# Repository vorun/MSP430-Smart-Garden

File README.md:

# MSP430-Smart-Garden

This project is a smart agricultural system based on C# using MSP430 microcontroller.

- Data coming from 3 sensors gets sent serially using bluetooth module from msp430 to computer and displayed at the
screen.

- Devices connected to msp430 which are lamp, fan, heater and 2 water pumps can be controlled from the
computer. Each button sends a different character and msp430 does operations acording to character it 
receives. Msp430 generates 3 different pwm signals to control fan and lamp for each setting which are 
low, medium and high. Heater can be oppened and closed. 2 water pumps can be oppened for 3 different 
amount times which are 3 seconds, 7 seconds and 10 seconds.

- Pin connections and circuit design/PCB of the project can be found at the 
"C# Based Smart Gardener Final PCB" folder.

For demo: https://www.youtube.com/watch?v=NzMayukbllw

Note
- Updated PCB with MOSFETs and gate drivers.

Orhun Dabak/Ahmet Özbaysar

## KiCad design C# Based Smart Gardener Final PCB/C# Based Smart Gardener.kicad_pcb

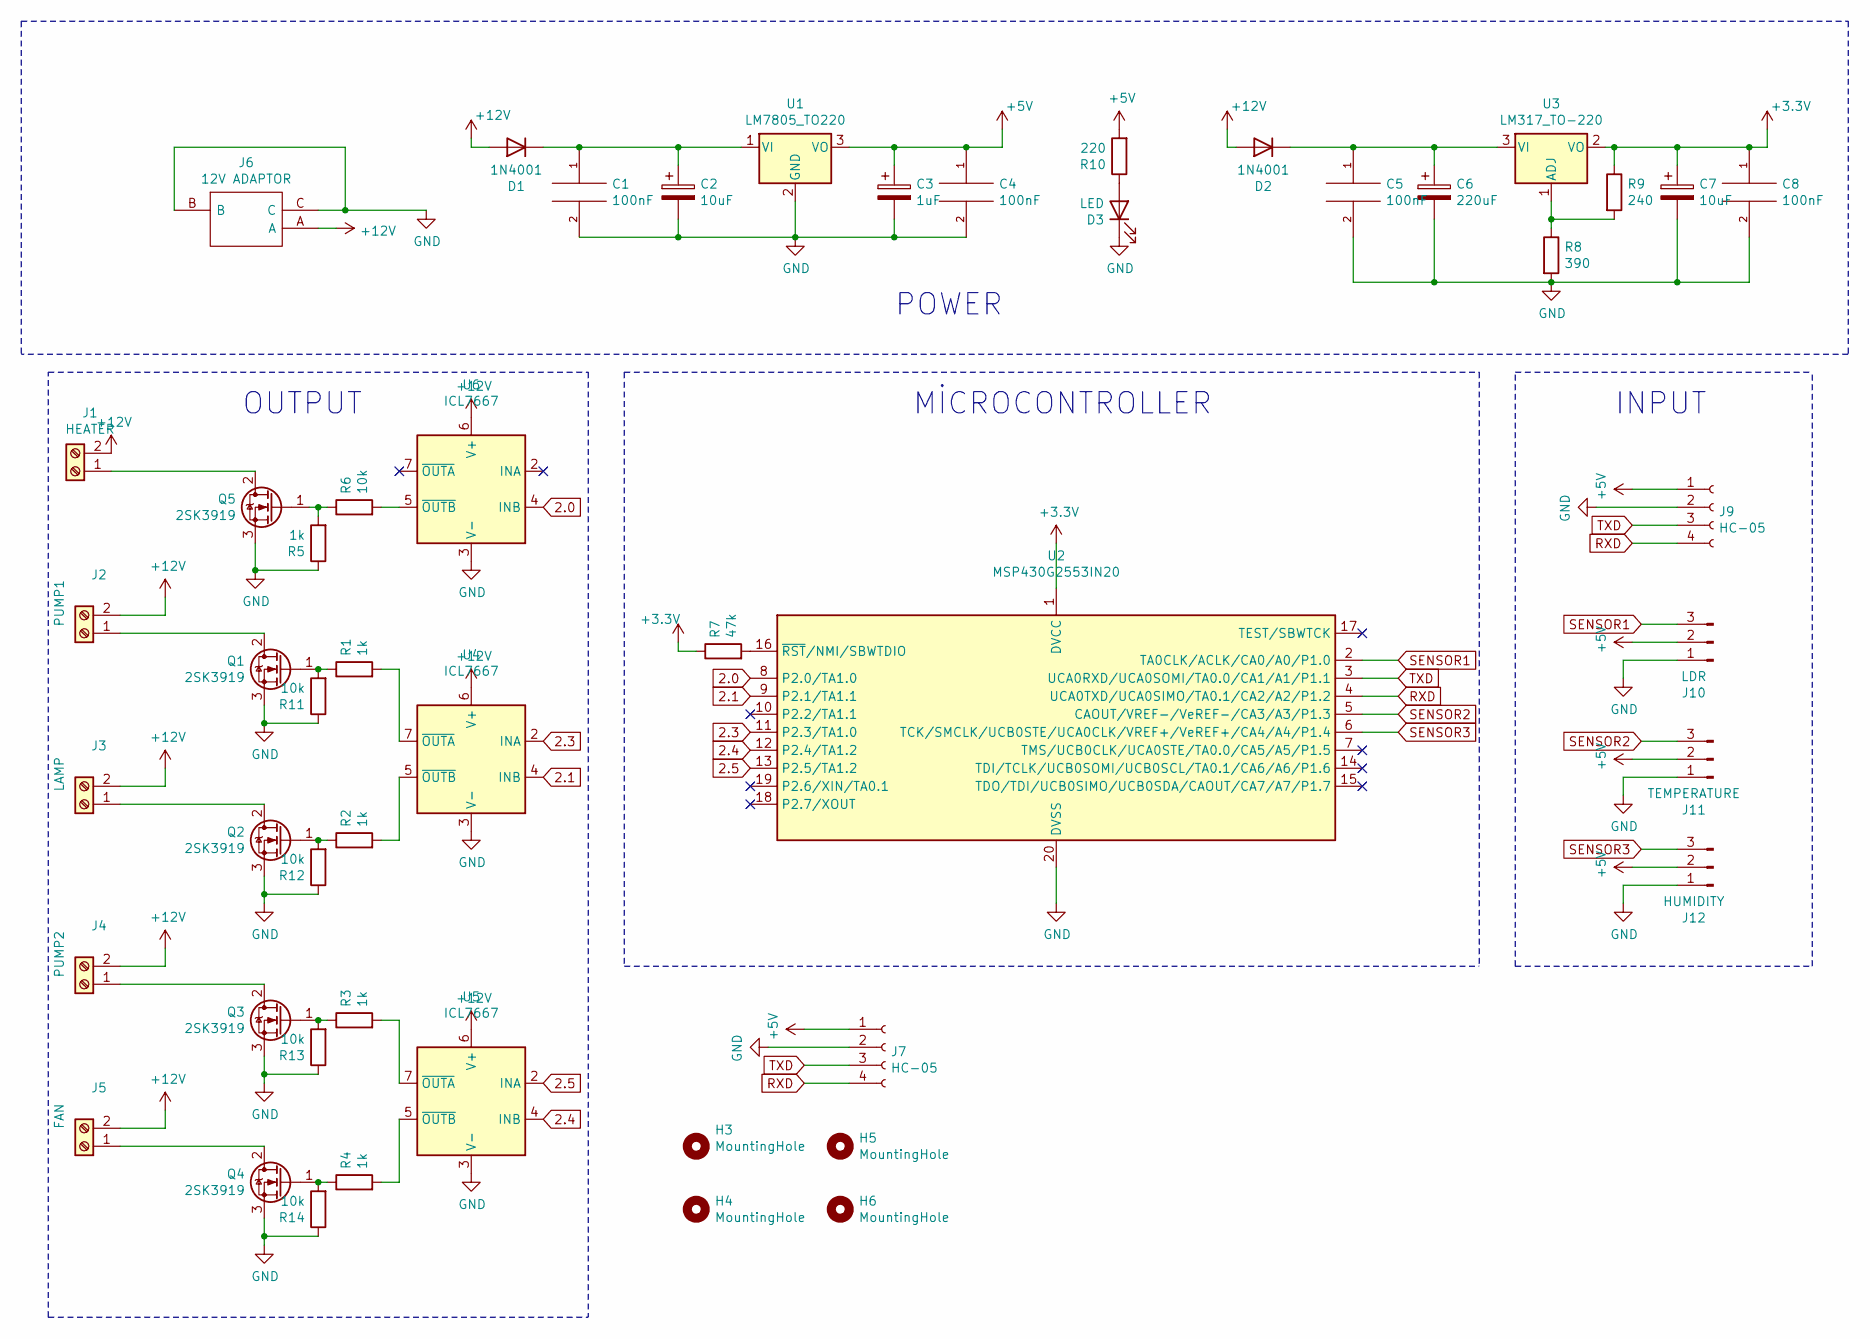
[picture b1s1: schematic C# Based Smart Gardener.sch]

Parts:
C1, C4, C5, C8: 100nF; C_1206_3216Metric_Pad1.33x1.80mm_HandSolder
C2, C7: 10uF; CP_EIA-3528-21_Kemet-B_Pad1.50x2.35mm_HandSolder
C3: 1uF; CP_EIA-3528-21_Kemet-B_Pad1.50x2.35mm_HandSolder
C6: 220uF; CP_EIA-7343-31_Kemet-D_Pad2.25x2.55mm_HandSolder
D1, D2: 1N4001; D_SOD-323_HandSoldering
D3: LED; LED_D5.0mm
H3, H4, H5, H6: MountingHole; MountingHole_3.2mm_M3_Pad_Via
J1: HEATER; TerminalBlock_Phoenix_MKDS-1,5-2_1x02_P5.00mm_Horizontal
J2: PUMP1; TerminalBlock_Phoenix_MKDS-1,5-2_1x02_P5.00mm_Horizontal
J3: LAMP; TerminalBlock_Phoenix_MKDS-1,5-2_1x02_P5.00mm_Horizontal
J4: PUMP2; TerminalBlock_Phoenix_MKDS-1,5-2_1x02_P5.00mm_Horizontal
J5: FAN; TerminalBlock_Phoenix_MKDS-1,5-2_1x02_P5.00mm_Horizontal
J6: 12V ADAPTOR; 163179PHEX; Manufacturer_Part_Number 163-179PH-EX; Mouser Part Number 163-179PH-EX
J7, J9: HC-05; PinSocket_1x04_P2.54mm_Vertical
J10: LDR; PinHeader_1x03_P2.54mm_Vertical
J11: TEMPERATURE; PinHeader_1x03_P2.54mm_Vertical
J12: HUMIDITY; PinHeader_1x03_P2.54mm_Vertical
Q1, Q2, Q3, Q4, Q5: 2SK3919; TO-252-2
R1, R2, R3, R4, R5: 1k; R_1210_3225Metric_Pad1.30x2.65mm_HandSolder
R6, R11, R12, R13, R14: 10k; R_1210_3225Metric_Pad1.30x2.65mm_HandSolder
R7: 47k; R_Axial_DIN0204_L3.6mm_D1.6mm_P5.08mm_Horizontal
R8: 390; R_1210_3225Metric_Pad1.30x2.65mm_HandSolder
R9: 240; R_1210_3225Metric_Pad1.30x2.65mm_HandSolder
R10: 220; R_Axial_DIN0204_L3.6mm_D1.6mm_P5.08mm_Horizontal
U1: LM7805_TO220; SOT-223-3_TabPin2
U2: MSP430G2553IN20; DIP-20_W7.62mm
U3: LM317_TO-220; SOT-223-3_TabPin2
U4, U5, U6: ICL7667; DIP-8_W7.62mm

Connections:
2.0: U2.8 (P2.0/TA1.0), U6.4 (INB)
2.1: U2.9 (P2.1/TA1.1), U4.4 (INB)
2.3: U2.11 (P2.3/TA1.0), U4.2 (INA)
2.4: U2.12 (P2.4/TA1.2), U5.4 (INB)
2.5: U2.13 (P2.5/TA1.2), U5.2 (INA)
+3V3: C7.1, C8.1, R7.1, R9.1, U2.1 (DVCC), U3.2 (VO)
+5V: C3.1, C4.1, J7.1, J9.1, J10.2, J11.2, J12.2, R10.2, U1.3 (VO)
+12V: D1.2 (A), D2.2 (A), J1.2, J2.2, J3.2, J4.2, J5.2, J6.A, U4.6 (V+), U5.6 (V+), U6.6 (V+)
GND: C1.2, C2.2, C3.2, C4.2, C5.2, C6.2, C7.2, C8.2, D3.1 (K), J6.B, J6.C, J7.2, J9.2, J10.1, J11.1, J12.1, Q1.3 (S), Q2.3 (S), Q3.3 (S), Q4.3 (S), Q5.3 (S), R5.1, R8.2, R11.1, R12.1, R13.1, R14.1, U1.2 (GND), U2.20 (DVSS), U4.3 (V-), U5.3 (V-), U6.3 (V-)
unnamed: C1.1, C2.1, D1.1 (K), U1.1 (VI)
unnamed: C5.1, C6.1, D2.1 (K), U3.3 (VI)
unnamed: D3.2 (A), R10.1
unnamed: J1.1, Q5.2 (D)
unnamed: J2.1, Q1.2 (D)
unnamed: J3.1, Q2.2 (D)
unnamed: J4.1, Q3.2 (D)
unnamed: J5.1, Q4.2 (D)
unnamed: Q1.1 (G), R1.1, R11.2
unnamed: Q2.1 (G), R2.1, R12.2
unnamed: Q3.1 (G), R3.1, R13.2
unnamed: Q4.1 (G), R4.1, R14.2
unnamed: Q5.1 (G), R5.2, R6.1
unnamed: R1.2, U4.7 (~OUTA)
unnamed: R2.2, U4.5 (~OUTB)
unnamed: R3.2, U5.7 (~OUTA)
unnamed: R4.2, U5.5 (~OUTB)
unnamed: R6.2, U6.5 (~OUTB)
unnamed: R7.2, U2.16 (~RST~/NMI/SBWTDIO)
unnamed: R8.1, R9.2, U3.1 (ADJ)
RXD: J7.4, J9.4, U2.4 (UCA0TXD/UCA0SIMO/TA0.1/CA2/A2/P1.2)
SENSOR1: J10.3, U2.2 (TA0CLK/ACLK/CA0/A0/P1.0)
SENSOR2: J11.3, U2.5 (CAOUT/VREF-/VeREF-/CA3/A3/P1.3)
SENSOR3: J12.3, U2.6 (TCK/SMCLK/UCB0STE/UCA0CLK/VREF+/VeREF+/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)
TXD: J7.3, J9.3, U2.3 (UCA0RXD/UCA0SOMI/TA0.0/CA1/A1/P1.1)

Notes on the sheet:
MİCROCONTROLLER
INPUT
OUTPUT
POWER

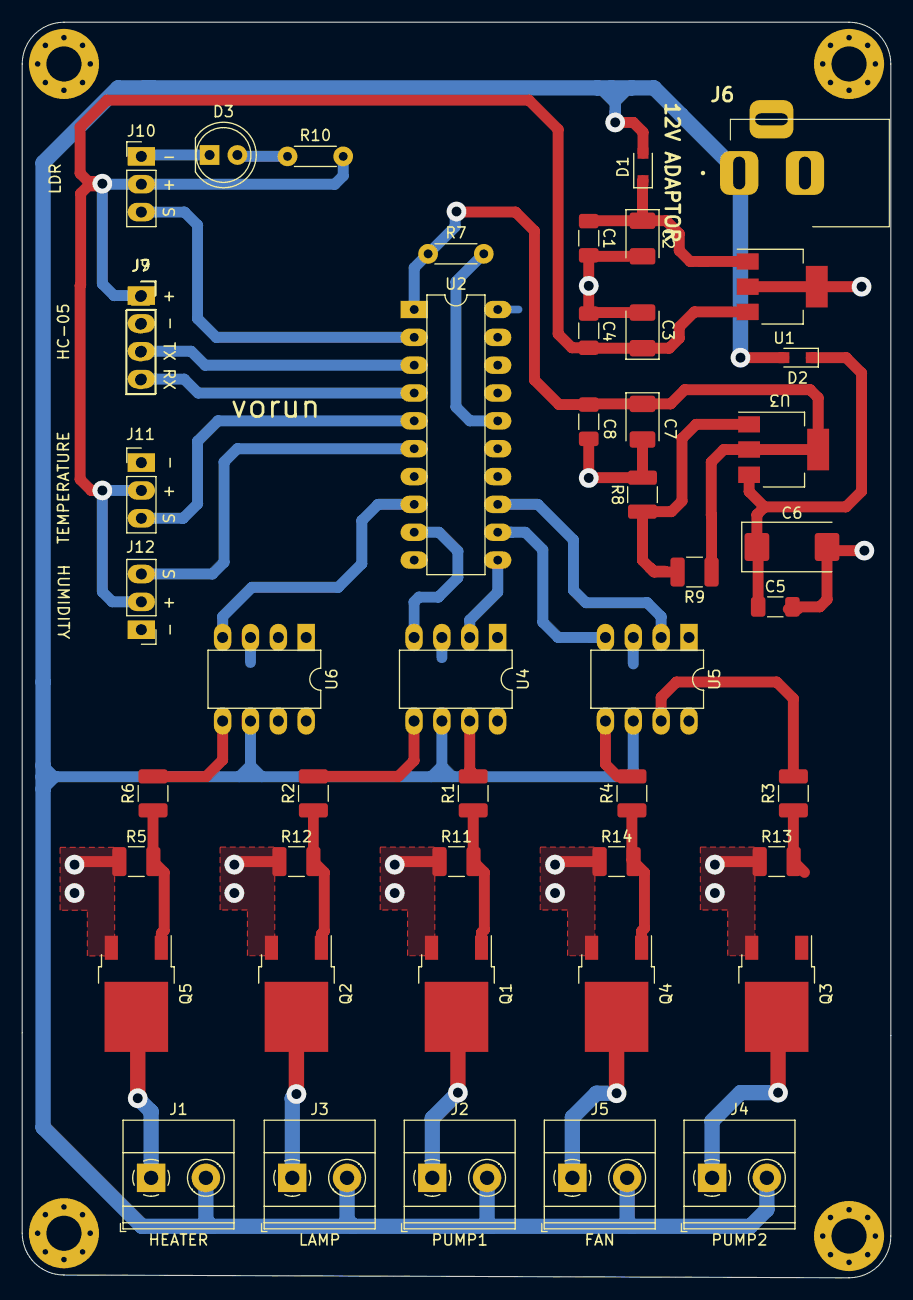
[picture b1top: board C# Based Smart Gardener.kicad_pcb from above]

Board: 2 copper layers, 79.2 x 114.6 mm, 51 parts (0 on the bottom side), 34 nets.

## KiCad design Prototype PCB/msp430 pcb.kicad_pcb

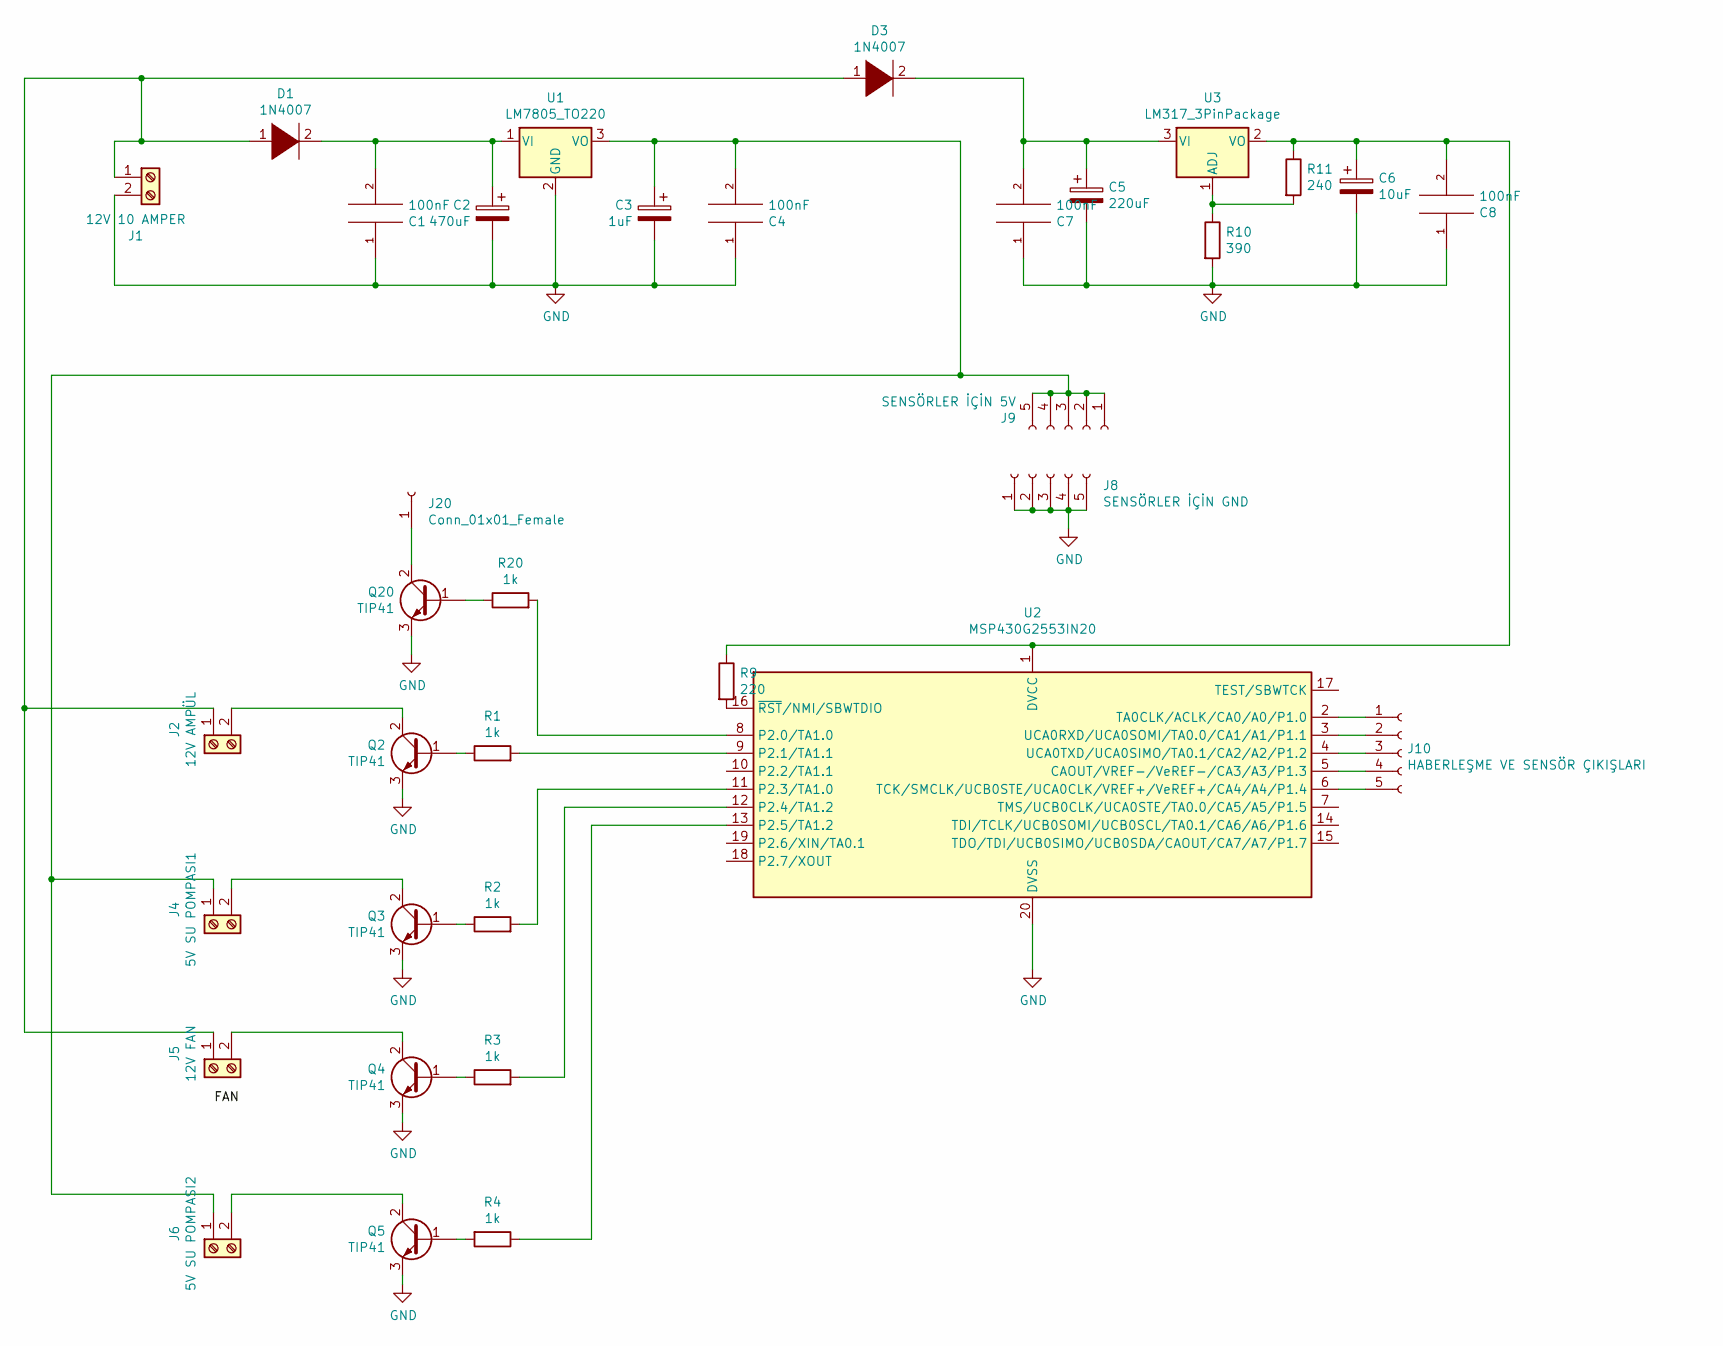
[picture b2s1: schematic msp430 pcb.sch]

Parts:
C1, C4, C7, C8: 100nF; CP_Radial_Tantal_D5.5mm_P5.00mm
C2: 470uF; CP_Radial_Tantal_D9.0mm_P5.00mm
C3: 1uF; CP_Radial_Tantal_D5.5mm_P5.00mm
C5: 220uF; CP_Radial_Tantal_D5.5mm_P5.00mm
C6: 10uF; CP_Radial_Tantal_D5.5mm_P5.00mm
D1: 1N4007; D_DO-41_SOD81_P7.62mm_Horizontal
D3: 1N4007; D_DO-41_SOD81_P10.16mm_Horizontal
J1: 12V 10 AMPER; TerminalBlock_Phoenix_MKDS-1,5-2_1x02_P5.00mm_Horizontal
J2: 12V AMPÜL; TerminalBlock_Phoenix_MKDS-1,5-2_1x02_P5.00mm_Horizontal
J4: 5V SU POMPASI1; TerminalBlock_Phoenix_MKDS-1,5-2_1x02_P5.00mm_Horizontal
J5: 12V FAN; TerminalBlock_Phoenix_MKDS-1,5-2_1x02_P5.00mm_Horizontal
J6: 5V SU POMPASI2; TerminalBlock_Phoenix_MKDS-1,5-2_1x02_P5.00mm_Horizontal
J8: SENSÖRLER İÇİN GND; PinHeader_1x05_P2.54mm_Vertical
J9: SENSÖRLER İÇİN 5V; PinHeader_1x05_P2.54mm_Vertical
J10: HABERLEŞME VE SENSÖR ÇIKIŞLARI; PinHeader_1x05_P2.54mm_Vertical
J20: Conn_01x01_Female; PinHeader_1x01_P2.54mm_Vertical
Q2, Q3, Q4, Q5, Q20: TIP41; TO-220-3_Vertical
R1, R2, R3, R4, R20: 1k; R_Axial_DIN0309_L9.0mm_D3.2mm_P12.70mm_Horizontal
R9: 220; R_Axial_DIN0309_L9.0mm_D3.2mm_P12.70mm_Horizontal
R10: 390; R_Axial_DIN0309_L9.0mm_D3.2mm_P12.70mm_Horizontal
R11: 240; R_Axial_DIN0309_L9.0mm_D3.2mm_P12.70mm_Horizontal
U1: LM7805_TO220; TO-220-3_Vertical
U2: MSP430G2553IN20; DIP-20_W7.62mm
U3: LM317_3PinPackage; TO-220-3_Vertical

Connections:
GND: C1.1, C2.2, C3.2, C4.1, C5.2, C6.2, C7.1, C8.1, J1.2, J8.1, J8.2, J8.3, J8.4, J8.5, Q2.3 (E), Q3.3 (E), Q4.3 (E), Q5.3 (E), Q20.3 (E), R10.2, U1.2 (GND), U2.20 (DVSS)
unnamed: C1.2, C2.1, D1.2 (A), U1.1 (VI)
unnamed: C3.1, C4.2, J4.1, J6.1, J9.1, J9.2, J9.3, J9.4, J9.5, U1.3 (VO)
unnamed: C5.1, C7.2, D3.2 (A), U3.3 (VI)
unnamed: C6.1, C8.2, R9.1, R11.1, U2.1 (DVCC), U3.2 (VO)
unnamed: D1.1 (K), D3.1 (K), J1.1, J2.1, J5.1
unnamed: J2.2, Q2.2 (C)
unnamed: J4.2, Q3.2 (C)
unnamed: J5.2, Q4.2 (C)
unnamed: J6.2, Q5.2 (C)
unnamed: J10.1, U2.2 (TA0CLK/ACLK/CA0/A0/P1.0)
unnamed: J10.2, U2.3 (UCA0RXD/UCA0SOMI/TA0.0/CA1/A1/P1.1)
unnamed: J10.3, U2.4 (UCA0TXD/UCA0SIMO/TA0.1/CA2/A2/P1.2)
unnamed: J10.4, U2.5 (CAOUT/VREF-/VeREF-/CA3/A3/P1.3)
unnamed: J10.5, U2.6 (TCK/SMCLK/UCB0STE/UCA0CLK/VREF+/VeREF+/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)
unnamed: J20.1, Q20.2 (C)
unnamed: Q2.1 (B), R1.1
unnamed: Q3.1 (B), R2.1
unnamed: Q4.1 (B), R3.1
unnamed: Q5.1 (B), R4.2
unnamed: Q20.1 (B), R20.1
unnamed: R1.2, U2.9 (P2.1/TA1.1)
unnamed: R2.2, U2.11 (P2.3/TA1.0)
unnamed: R3.2, U2.12 (P2.4/TA1.2)
unnamed: R4.1, U2.13 (P2.5/TA1.2)
unnamed: R9.2, U2.16 (~RST~/NMI/SBWTDIO)
unnamed: R10.1, R11.2, U3.1 (ADJ)
unnamed: R20.2, U2.8 (P2.0/TA1.0)

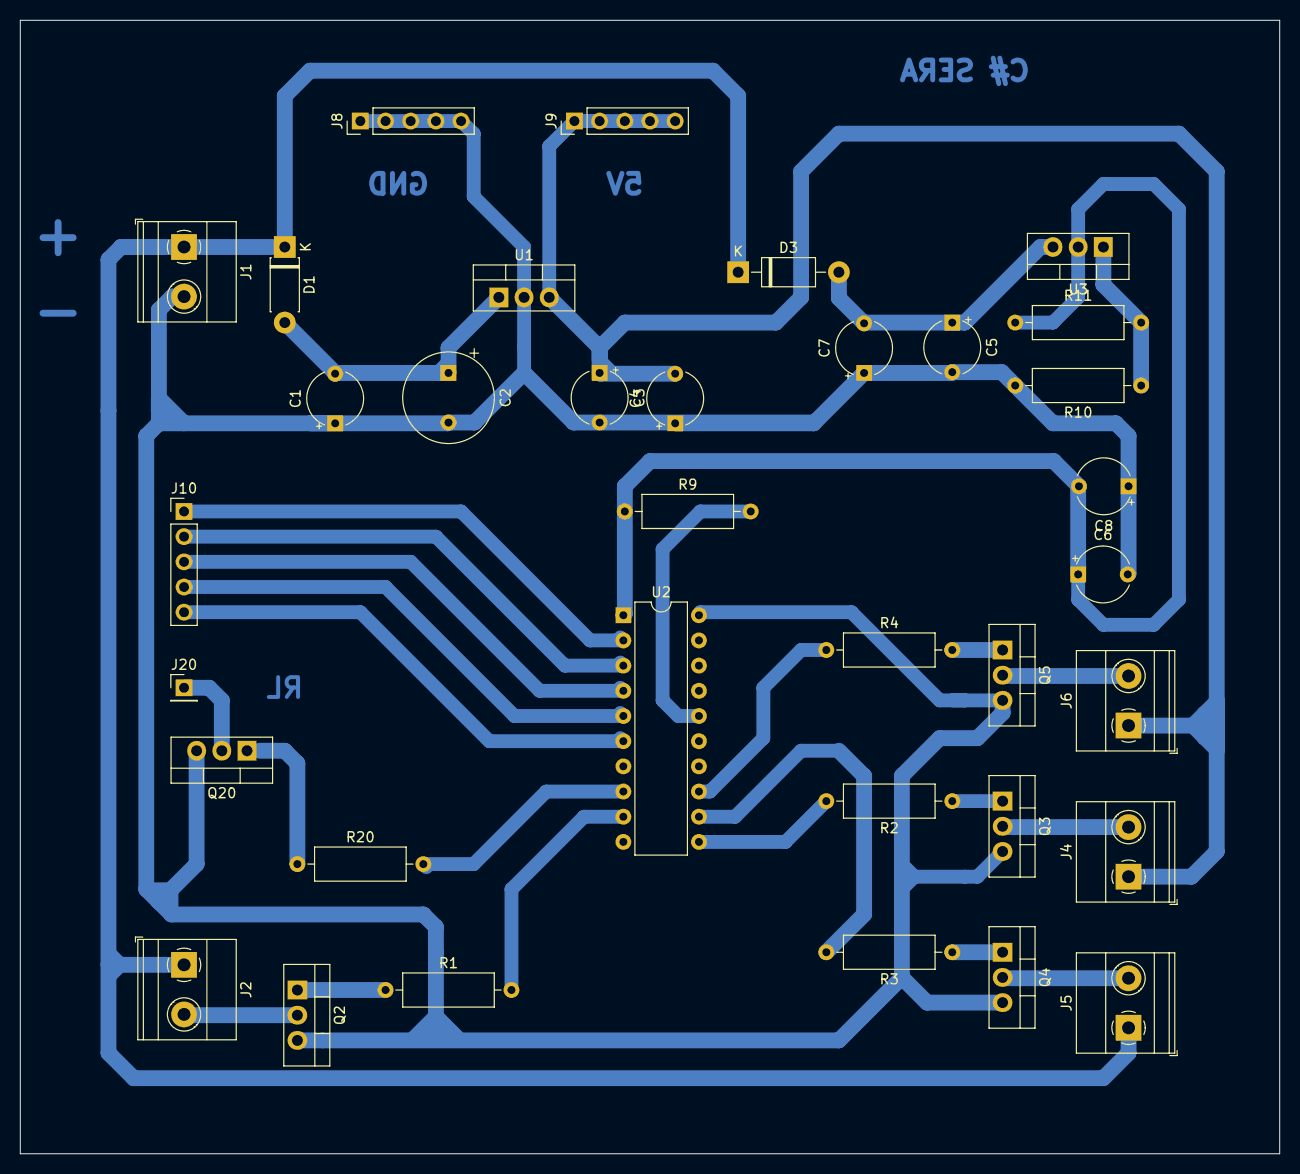
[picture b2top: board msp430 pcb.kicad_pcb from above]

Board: 2 copper layers, 127.0 x 114.3 mm, 35 parts (0 on the bottom side), 28 nets.

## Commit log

2022-03-26 PCB Update
2022-06-18 Update PCB
2022-06-25 PCB Updated
2022-06-29 3D Updated
